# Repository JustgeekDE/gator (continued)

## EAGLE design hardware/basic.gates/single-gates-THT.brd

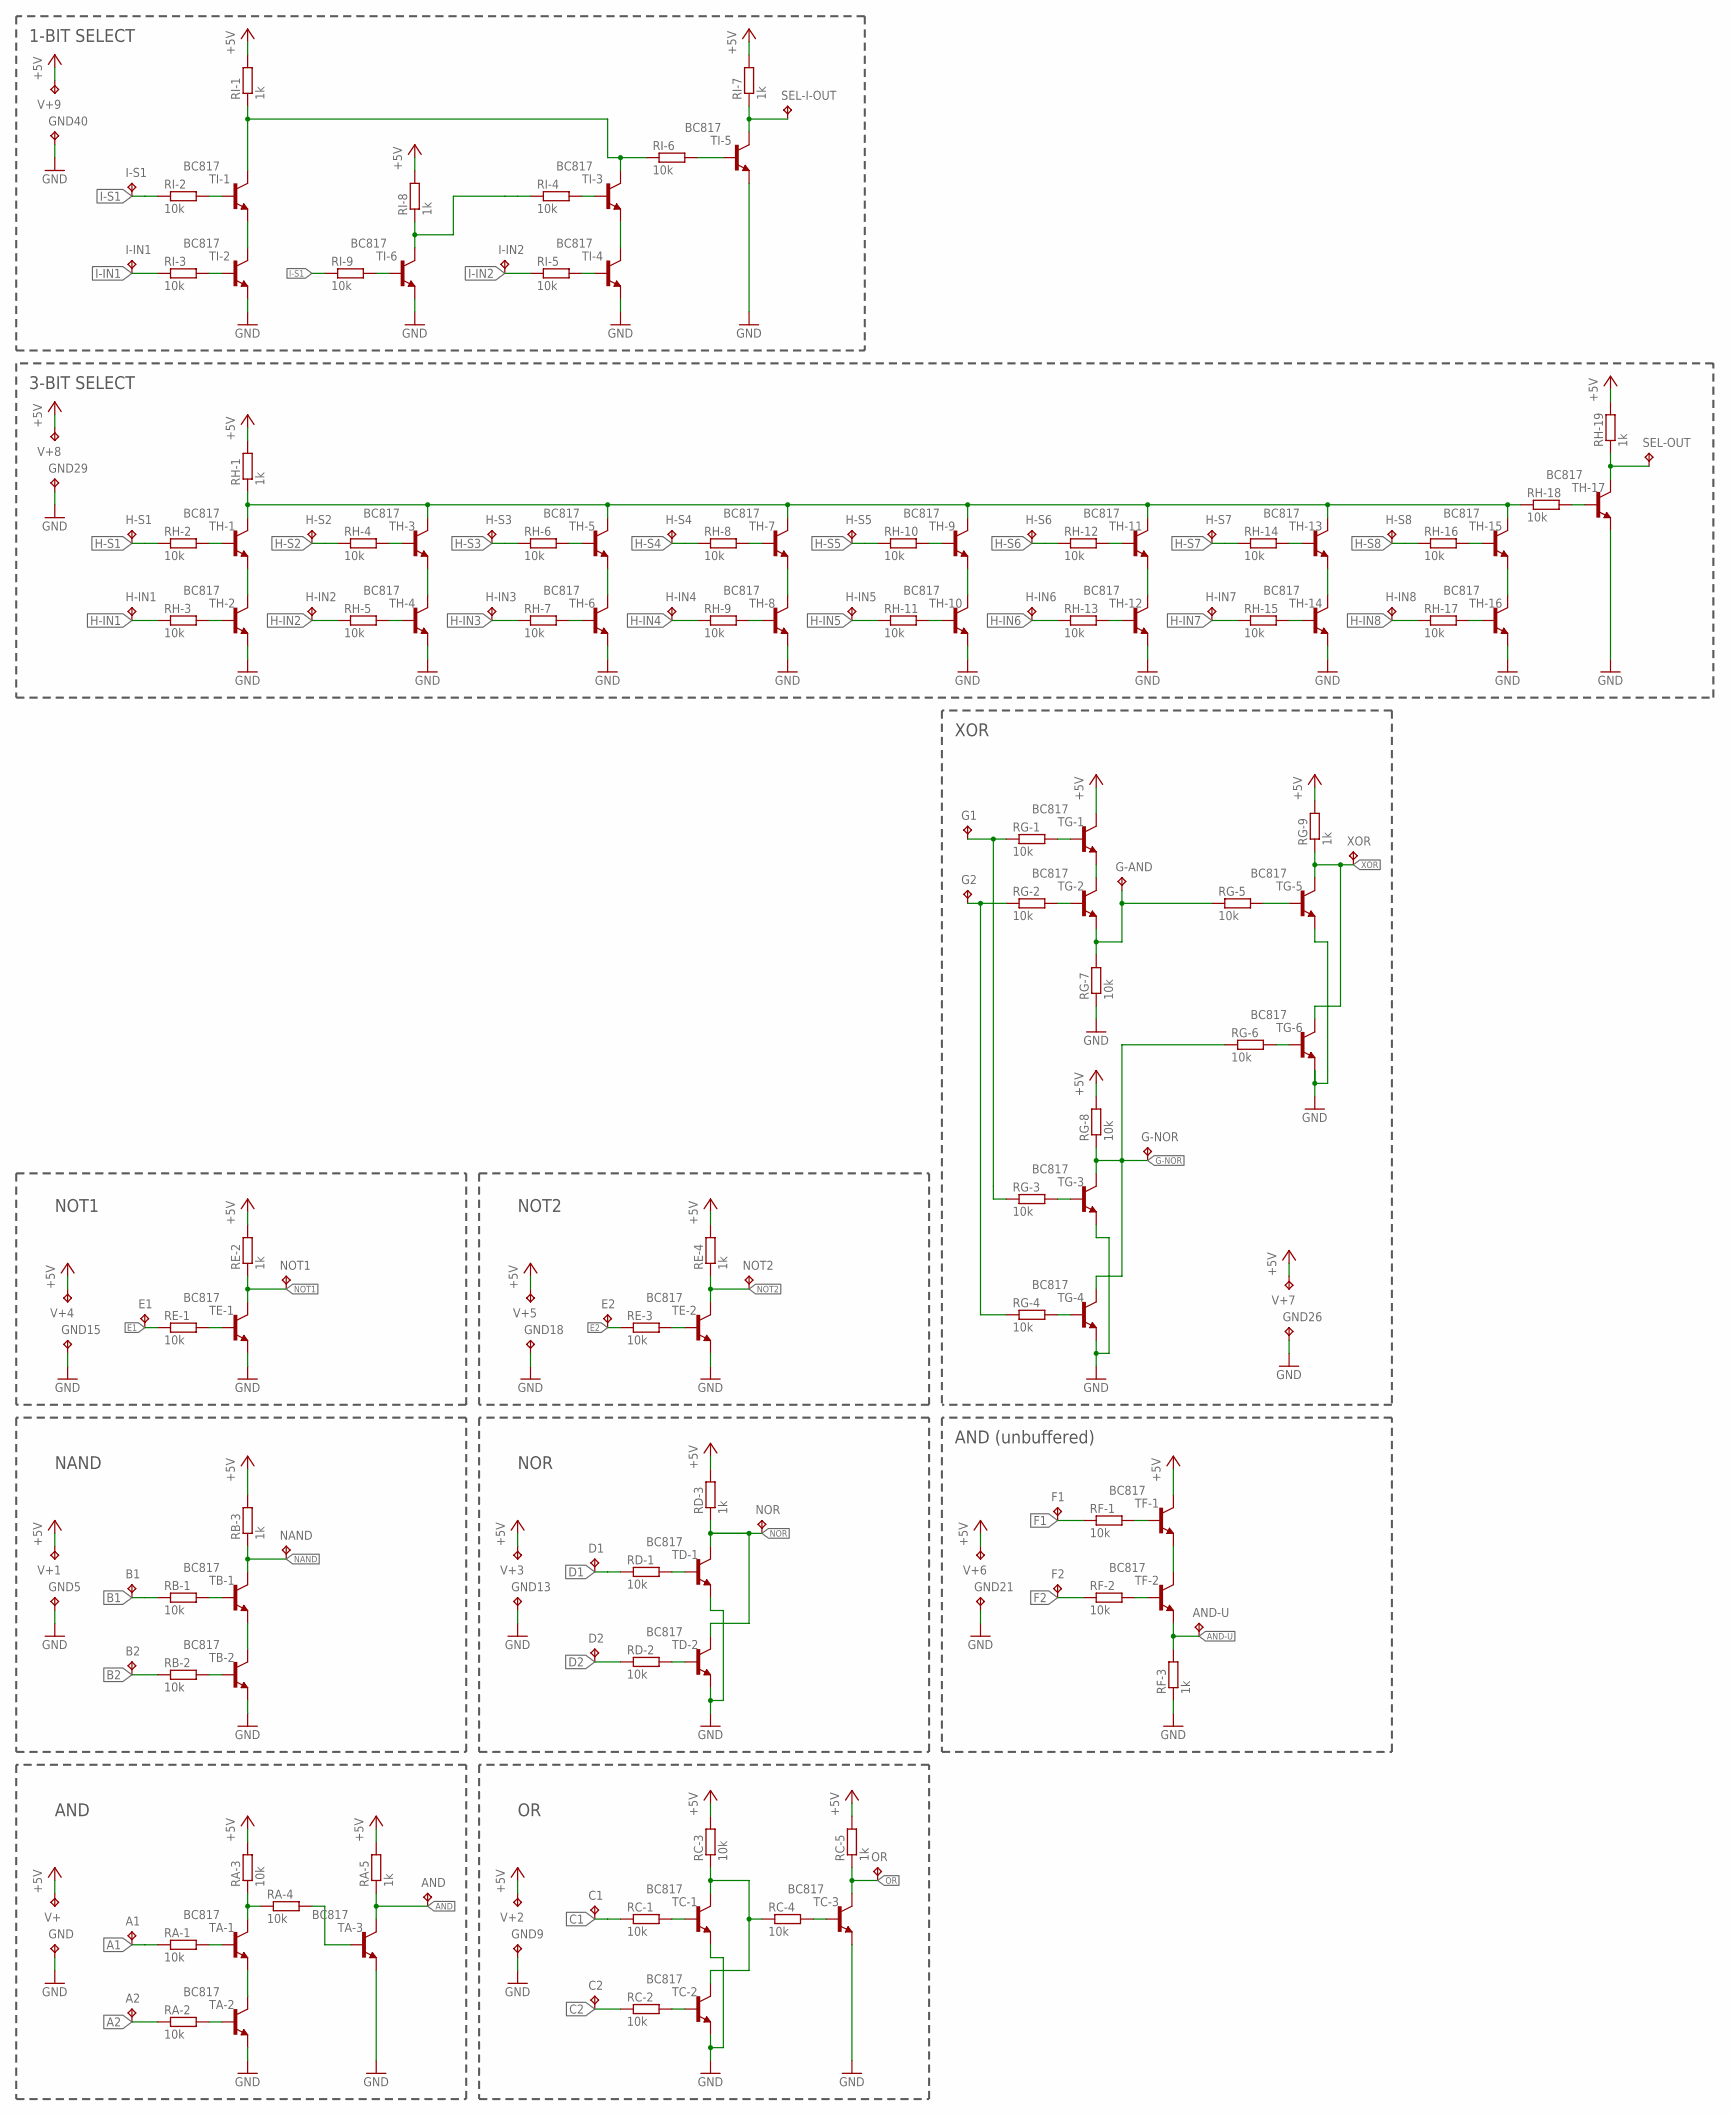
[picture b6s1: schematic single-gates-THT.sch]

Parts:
A1, A2: TPTP07R; TP07R
AND: TPTP07R; TP07R
AND-U: TPTP07R; TP07R
B1, B2: TPTP07R; TP07R
C1, C2: TPTP07R; TP07R
D1, D2: TPTP07R; TP07R
E1, E2: TPTP07R; TP07R
F1, F2: TPTP07R; TP07R
G1, G2: TPTP07R; TP07R
G-AND: TPTP07R; TP07R
G-NOR: TPTP07R; TP07R
GND, GND5, GND9, GND13, GND15, GND18, GND21, GND26, GND29, GND40: TPTP07R; TP07R
H-IN1, H-IN2, H-IN3, H-IN4, H-IN5, H-IN6, H-IN7, H-IN8: TPTP07R; TP07R
H-S1, H-S2, H-S3, H-S4, H-S5, H-S6, H-S7, H-S8: TPTP07R; TP07R
I-IN1, I-IN2: TPTP07R; TP07R
I-S1: TPTP07R; TP07R
NAND: TPTP07R; TP07R
NOR: TPTP07R; TP07R
NOT1, NOT2: TPTP07R; TP07R
OR: TPTP07R; TP07R
RA-1, RA-2, RA-3, RA-4: 10k; 0207/7
RA-5: 1k; 0207/7
RB-1, RB-2: 10k; 0207/7
RB-3: 1k; 0207/7
RC-1, RC-2, RC-3, RC-4: 10k; 0207/7
RC-5: 1k; 0207/7
RD-1, RD-2: 10k; 0207/7
RD-3: 1k; 0207/7
RE-1, RE-3: 10k; 0207/7
RE-2, RE-4: 1k; 0207/7
RF-1, RF-2: 10k; 0207/7
RF-3: 1k; 0207/7
RG-1, RG-2, RG-3, RG-4, RG-5, RG-6, RG-7, RG-8: 10k; 0207/7
RG-9: 1k; 0207/7
RH-1, RH-19: 1k; 0207/7
RH-2, RH-3, RH-4, RH-5, RH-6, RH-7, RH-8, RH-9, RH-10, RH-11, RH-12, RH-13, RH-14, RH-15, RH-16, RH-17, RH-18: 10k; 0207/7
RI-1, RI-7, RI-8: 1k; 0207/7
RI-2, RI-3, RI-4, RI-5, RI-6, RI-9: 10k; 0207/7
SEL-I-OUT: TPTP07R; TP07R
SEL-OUT: TPTP07R; TP07R
TA-1, TA-2, TA-3: BC817; TO92
TB-1, TB-2: BC817; TO92
TC-1, TC-2, TC-3: BC817; TO92
TD-1, TD-2: BC817; TO92
TE-1, TE-2: BC817; TO92
TF-1, TF-2: BC817; TO92
TG-1, TG-2, TG-3, TG-4, TG-5, TG-6: BC817; TO92
TH-1, TH-2, TH-3, TH-4, TH-5, TH-6, TH-7, TH-8, TH-9, TH-10, TH-11, TH-12, TH-13, TH-14, TH-15, TH-16, TH-17: BC817; TO92
TI-1, TI-2, TI-3, TI-4, TI-5, TI-6: BC817; TO92
V+, V+1, V+2, V+3, V+4, V+5, V+6, V+7, V+8, V+9: TPTP07R; TP07R
XOR: TPTP07R; TP07R

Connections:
+5V: RA-3.2, RA-5.2, RB-3.2, RC-3.2, RC-5.2, RD-3.2, RE-2.2, RE-4.2, RG-8.2, RG-9.2, RH-1.2, RH-19.2, RI-1.2, RI-7.2, RI-8.2, TF-1.3 (C), TG-1.3 (C), V+.TP, V+1.TP, V+2.TP, V+3.TP, V+4.TP, V+5.TP, V+6.TP, V+7.TP, V+8.TP, V+9.TP
A1: A1.TP, RA-1.1
A2: A2.TP, RA-2.1
AND: AND.TP, RA-5.1, TA-3.3 (C)
AND-U: AND-U.TP, RF-3.2, TF-2.1 (E)
B1: B1.TP, RB-1.1
B2: B2.TP, RB-2.1
C1: C1.TP, RC-1.1
C2: C2.TP, RC-2.1
D1: D1.TP, RD-1.1
D2: D2.TP, RD-2.1
E1: E1.TP, RE-1.1
E2: E2.TP, RE-3.1
F1: F1.TP, RF-1.1
F2: F2.TP, RF-2.1
G-AND: G-AND.TP, RG-5.1, RG-7.2, TG-2.1 (E)
G-NOR: G-NOR.TP, RG-6.1, RG-8.1, TG-3.3 (C), TG-4.3 (C)
GND: GND.TP, GND5.TP, GND9.TP, GND13.TP, GND15.TP, GND18.TP, GND21.TP, GND26.TP, GND29.TP, GND40.TP, RF-3.1, RG-7.1, TA-2.1 (E), TA-3.1 (E), TB-2.1 (E), TC-1.1 (E), TC-2.1 (E), TC-3.1 (E), TD-1.1 (E), TD-2.1 (E), TE-1.1 (E), TE-2.1 (E), TG-3.1 (E), TG-4.1 (E), TG-5.1 (E), TG-6.1 (E), TH-2.1 (E), TH-4.1 (E), TH-6.1 (E), TH-8.1 (E), TH-10.1 (E), TH-12.1 (E), TH-14.1 (E), TH-16.1 (E), TH-17.1 (E), TI-2.1 (E), TI-4.1 (E), TI-5.1 (E), TI-6.1 (E)
H-IN1: H-IN1.TP, RH-3.1
H-IN2: H-IN2.TP, RH-5.1
H-IN3: H-IN3.TP, RH-7.1
H-IN4: H-IN4.TP, RH-9.1
H-IN5: H-IN5.TP, RH-11.1
H-IN6: H-IN6.TP, RH-13.1
H-IN7: H-IN7.TP, RH-15.1
H-IN8: H-IN8.TP, RH-17.1
H-S1: H-S1.TP, RH-2.1
H-S2: H-S2.TP, RH-4.1
H-S3: H-S3.TP, RH-6.1
H-S4: H-S4.TP, RH-8.1
H-S5: H-S5.TP, RH-10.1
H-S6: H-S6.TP, RH-12.1
H-S7: H-S7.TP, RH-14.1
H-S8: H-S8.TP, RH-16.1
I-IN1: I-IN1.TP, RI-3.1
I-IN2: I-IN2.TP, RI-5.1
I-S1: I-S1.TP, RI-2.1, RI-9.1
I-S2: RI-4.1, RI-8.1, TI-6.3 (C)
unnamed: RA-1.2, TA-1.2 (B)
unnamed: RA-3.1, RA-4.1, TA-1.3 (C)
unnamed: RA-2.2, TA-2.2 (B)
unnamed: TA-1.1 (E), TA-2.3 (C)
unnamed: RB-1.2, TB-1.2 (B)
unnamed: RB-2.2, TB-2.2 (B)
unnamed: RC-1.2, TC-1.2 (B)
unnamed: TB-1.1 (E), TB-2.3 (C)
unnamed: RC-2.2, TC-2.2 (B)
unnamed: RC-4.2, TC-3.2 (B)
unnamed: RC-3.1, RC-4.1, TC-1.3 (C), TC-2.3 (C)
unnamed: RD-1.2, TD-1.2 (B)
unnamed: RD-2.2, TD-2.2 (B)
unnamed: RE-1.2, TE-1.2 (B)
unnamed: RA-4.2, TA-3.2 (B)
unnamed: RE-3.2, TE-2.2 (B)
unnamed: RF-1.2, TF-1.2 (B)
unnamed: RF-2.2, TF-2.2 (B)
unnamed: TG-1.1 (E), TG-2.3 (C)
unnamed: TF-1.1 (E), TF-2.3 (C)
unnamed: RG-1.2, TG-1.2 (B)
unnamed: RG-2.2, TG-2.2 (B)
unnamed: RG-4.2, TG-4.2 (B)
unnamed: RG-3.2, TG-3.2 (B)
unnamed: RG-6.2, TG-6.2 (B)
unnamed: RG-5.2, TG-5.2 (B)
unnamed: RH-2.2, TH-1.2 (B)
unnamed: RH-3.2, TH-2.2 (B)
unnamed: TH-1.1 (E), TH-2.3 (C)
unnamed: G1.TP, RG-1.1, RG-3.1
unnamed: G2.TP, RG-2.1, RG-4.1
unnamed: RH-4.2, TH-3.2 (B)
unnamed: RH-5.2, TH-4.2 (B)
unnamed: TH-3.1 (E), TH-4.3 (C)
unnamed: RH-6.2, TH-5.2 (B)
unnamed: RH-7.2, TH-6.2 (B)
unnamed: TH-5.1 (E), TH-6.3 (C)
unnamed: RH-8.2, TH-7.2 (B)
unnamed: RH-9.2, TH-8.2 (B)
unnamed: TH-7.1 (E), TH-8.3 (C)
unnamed: RH-10.2, TH-9.2 (B)
unnamed: RH-11.2, TH-10.2 (B)
unnamed: TH-9.1 (E), TH-10.3 (C)
unnamed: RH-12.2, TH-11.2 (B)
unnamed: RH-13.2, TH-12.2 (B)
unnamed: TH-11.1 (E), TH-12.3 (C)
unnamed: RH-14.2, TH-13.2 (B)
unnamed: RH-15.2, TH-14.2 (B)
unnamed: TH-13.1 (E), TH-14.3 (C)
unnamed: RH-16.2, TH-15.2 (B)
unnamed: RH-17.2, TH-16.2 (B)
unnamed: TH-15.1 (E), TH-16.3 (C)
unnamed: RI-2.2, TI-1.2 (B)
unnamed: RH-18.2, TH-17.2 (B)
unnamed: RI-3.2, TI-2.2 (B)
unnamed: TI-1.1 (E), TI-2.3 (C)
unnamed: RI-4.2, TI-3.2 (B)
unnamed: RI-5.2, TI-4.2 (B)
unnamed: TI-3.1 (E), TI-4.3 (C)
unnamed: RI-6.2, TI-5.2 (B)
unnamed: RI-9.2, TI-6.2 (B)
NAND: NAND.TP, RB-3.1, TB-1.3 (C)
NOR: NOR.TP, RD-3.1, TD-1.3 (C), TD-2.3 (C)
NOT1: NOT1.TP, RE-2.1, TE-1.3 (C)
NOT2: NOT2.TP, RE-4.1, TE-2.3 (C)
OR: OR.TP, RC-5.1, TC-3.3 (C)
SEL_INT: RH-1.1, RH-18.1, TH-1.3 (C), TH-3.3 (C), TH-5.3 (C), TH-7.3 (C), TH-9.3 (C), TH-11.3 (C), TH-13.3 (C), TH-15.3 (C)
SEL_INT1: RI-1.1, RI-6.1, TI-1.3 (C), TI-3.3 (C)
SEL_OUT: RH-19.1, SEL-OUT.TP, TH-17.3 (C)
SEL_OUT1: RI-7.1, SEL-I-OUT.TP, TI-5.3 (C)
XOR: RG-9.1, TG-5.3 (C), TG-6.3 (C), XOR.TP

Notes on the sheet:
AND
NAND
NOR
NOT1
NOT2
AND (unbuffered)
XOR
3-BIT SELECT
1-BIT SELECT

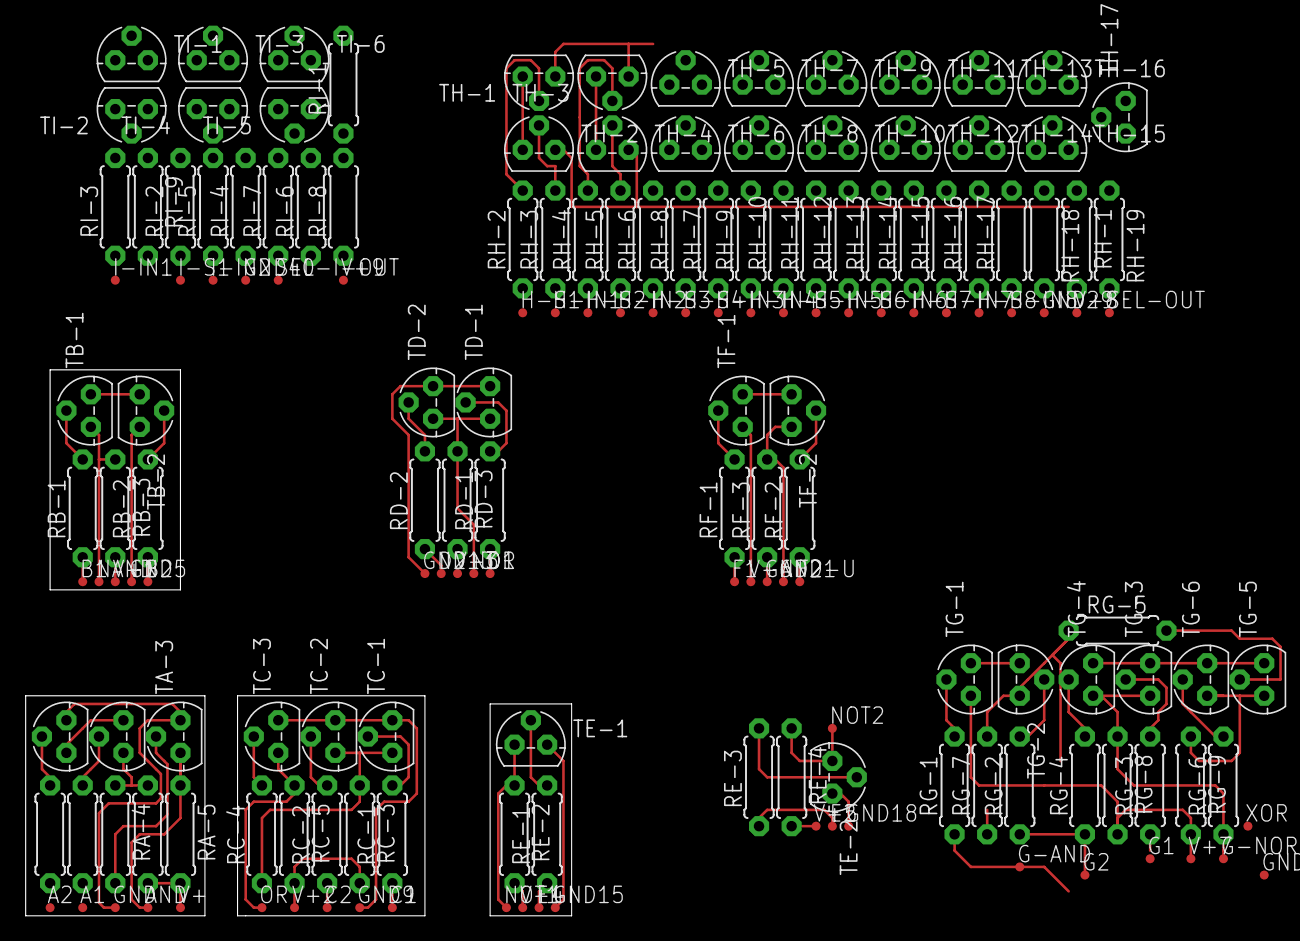
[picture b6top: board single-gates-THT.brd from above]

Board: 2 copper layers, 42.5 x 42.5 mm, 168 parts (0 on the bottom side), 109 nets.

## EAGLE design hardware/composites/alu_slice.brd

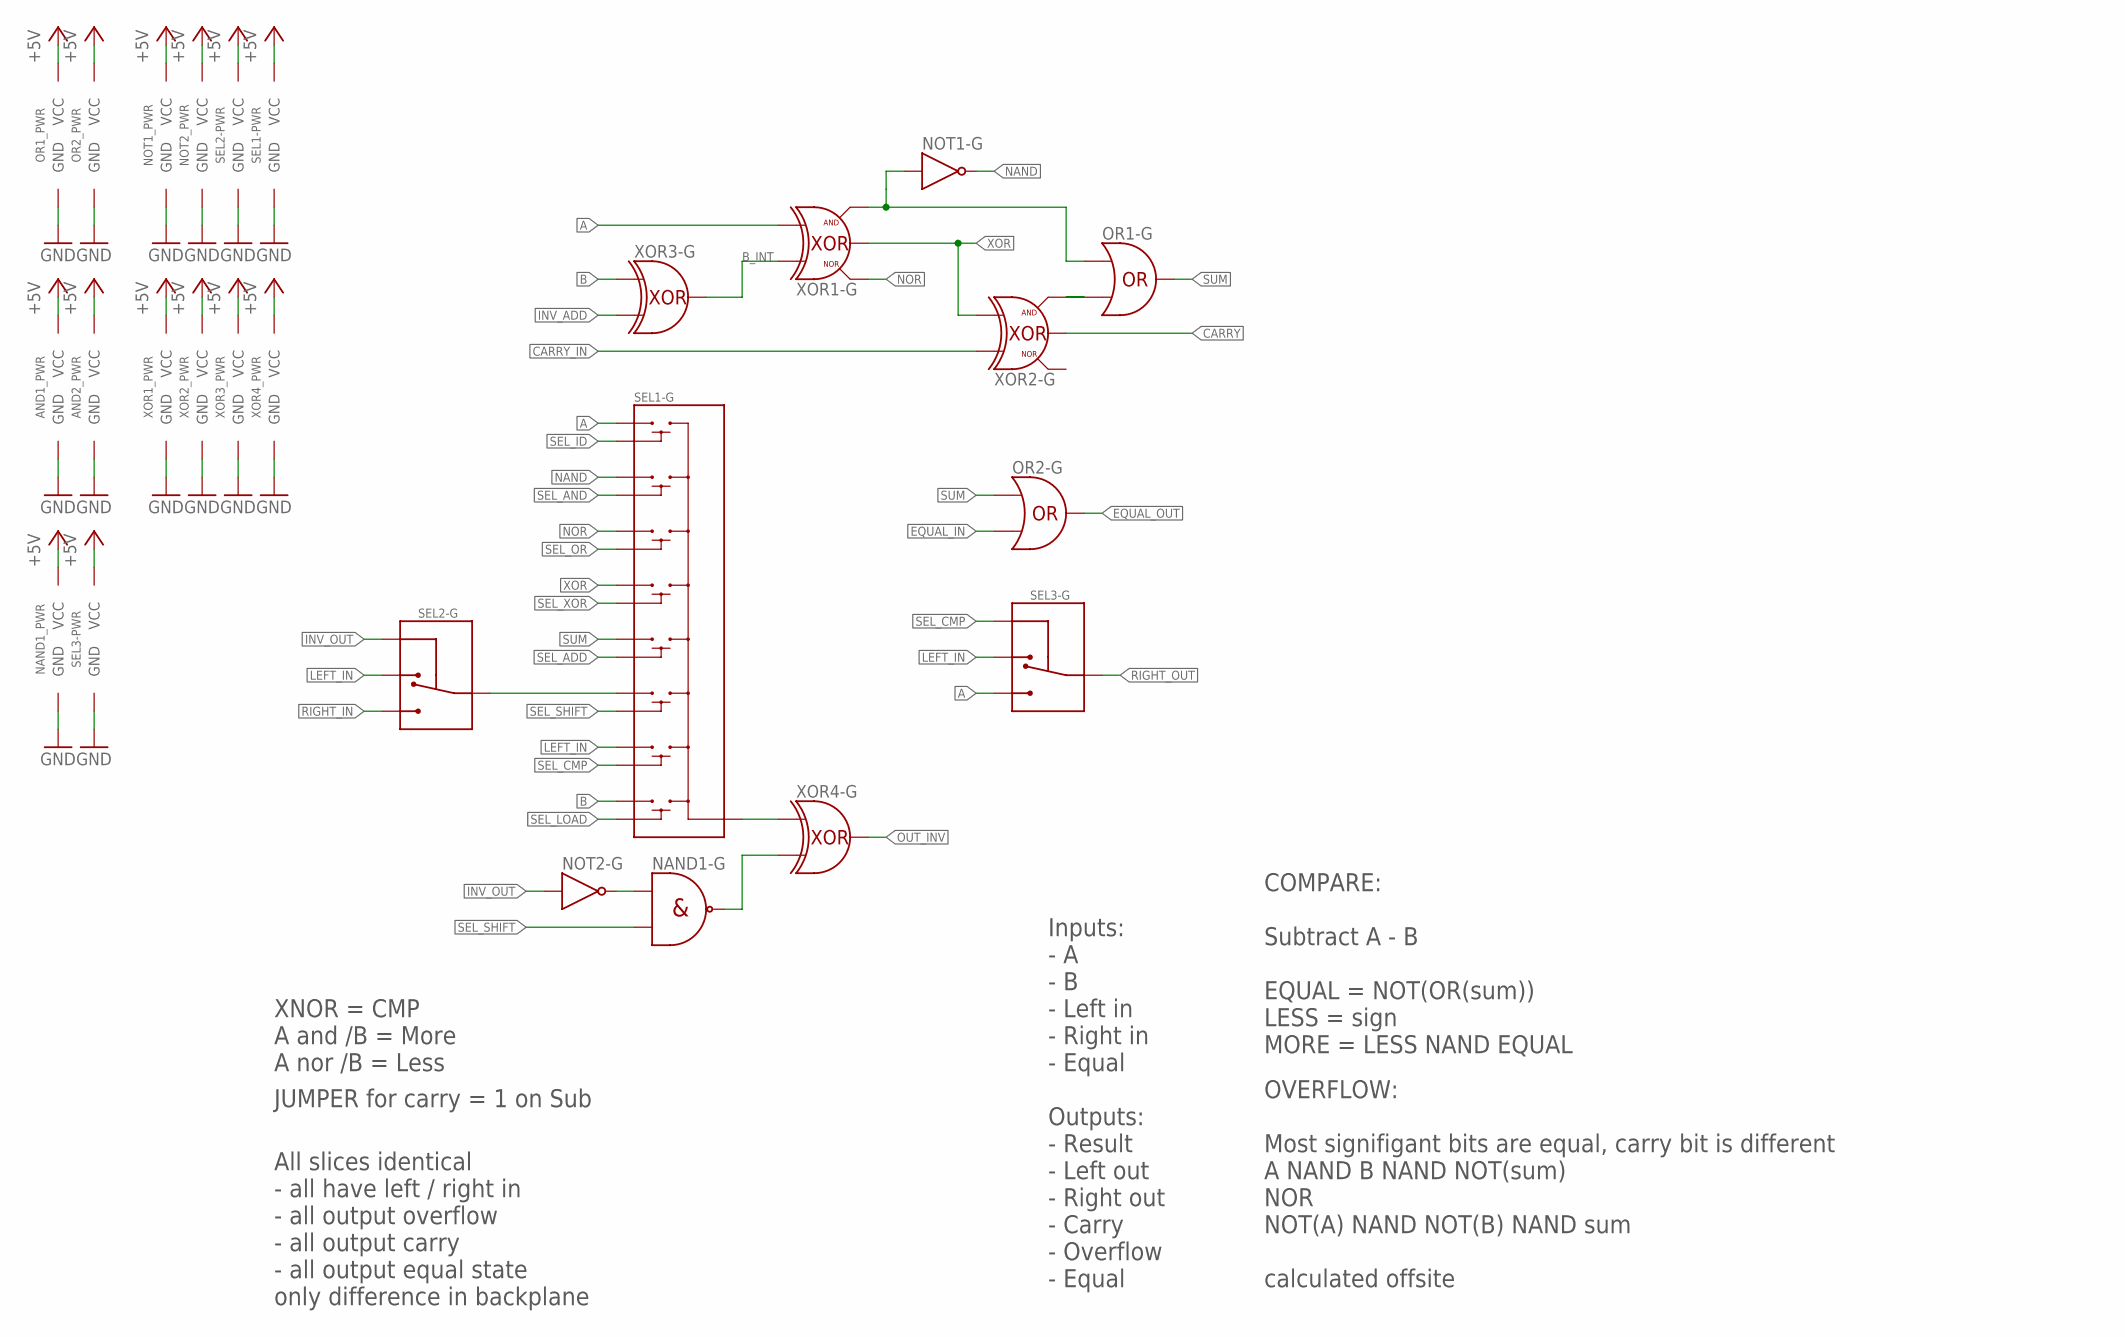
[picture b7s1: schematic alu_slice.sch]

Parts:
AND1, AND2: AND-UNBUF; AND-2-UNBUF
NAND1: NAND; NAND-2
NOT1, NOT2: NOT-VERTICAL
OR1, OR2: OR; OR-2
SEL1: SELECTOR; SELECTOR-8_BIT-NOMUX
SEL2, SEL3: SELECTOR-2_LANES; SELECTOR-2-LANE-NOMUX
XOR1, XOR2: EX-XOR; XOR-2-EX2
XOR3, XOR4: XOR; XOR-2-EX2

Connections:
+5V: AND1.OUT3 (VCC), AND2.OUT3 (VCC), NAND1.OUT1 (VCC), NOT1.OUT3 (VCC), NOT2.OUT3 (VCC), OR1.OUT3 (VCC), OR2.OUT3 (VCC), SEL1.V+ (VCC), SEL2.V+ (VCC), SEL3.V+ (VCC), XOR1.OUT1 (VCC), XOR2.OUT1 (VCC), XOR3.OUT1 (VCC), XOR4.OUT1 (VCC)
A: SEL1.IN1, SEL3.IN2, XOR1.B
B: SEL1.IN8, XOR3.A
B_INT: XOR1.A, XOR3.OUT4 (OUT)
CARRY: XOR2.OUT4 (OUT)
CARRY_IN: XOR2.A
EQUAL_IN: OR2.B
EQUAL_OUT: OR2.OUT1 (OUT)
GND: AND1.OUT1 (GND), AND2.OUT1 (GND), NAND1.OUT3 (GND), NOT1.OUT2 (GND), NOT2.OUT2 (GND), OR1.OUT2 (GND), OR2.OUT2 (GND), SEL1.GND, SEL2.GND, SEL3.GND, XOR1.OUT5 (GND), XOR2.OUT5 (GND), XOR3.OUT5 (GND), XOR4.OUT5 (GND)
INV_ADD: XOR3.B
INV_OUT: NOT2.IN, SEL2.SEL
LEFT_IN: SEL1.IN7, SEL2.IN1, SEL3.IN1
unnamed: NOT1.IN, OR1.A, XOR1.OUT2 (AND)
unnamed: OR1.B, XOR2.OUT2 (AND)
unnamed: SEL1.IN6, SEL2.OUT
unnamed: NAND1.OUT2 (OUT), XOR4.B
unnamed: NAND1.B (A), NOT2.OUT1 (OUT)
NAND: NOT1.OUT1 (OUT), SEL1.IN2
NOR: SEL1.IN3, XOR1.OUT3 (NOR)
OUT: SEL1.OUT, XOR4.A
OUT_INV: XOR4.OUT4 (OUT)
RIGHT_IN: SEL2.IN2
RIGHT_OUT: SEL3.OUT
SEL_ADD: SEL1.SEL5
SEL_AND: SEL1.SEL2
SEL_CMP: SEL1.SEL7, SEL3.SEL
SEL_ID: SEL1.SEL1
SEL_LOAD: SEL1.SEL8
SEL_OR: SEL1.SEL3
SEL_SHIFT: NAND1.A (B), SEL1.SEL6
SEL_XOR: SEL1.SEL4
SUM: OR1.OUT1 (OUT), OR2.A, SEL1.IN5
XOR: SEL1.IN4, XOR1.OUT4 (OUT), XOR2.B

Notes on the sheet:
XNOR = CMP
A and /B = More A nor /B = Less
JUMPER for carry = 1 on Sub
All slices identical - all have left / right in - all output overflow - all output carry - all output equal state only difference in backplane
Inputs: - A - B - Left in - Right in - Equal Outputs: - Result - Left out - Right out - Carry - Overflow - Equal
COMPARE: Subtract A - B EQUAL = NOT(OR(sum)) LESS = sign MORE = LESS NAND EQUAL
OVERFLOW: Most signifigant bits are equal, carry bit is different A NAND B NAND NOT(sum) NOR NOT(A) NAND NOT(B) NAND sum calculated offsite

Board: 2 copper layers, 14 parts (0 on the bottom side), 19 nets, no tracks yet.

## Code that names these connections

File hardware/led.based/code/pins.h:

#ifndef __PINS_H
#define __PINS_H


#define SET_BIT(port,bit)   (port |=  (1 << bit))
#define CLEAR_BIT(port,bit) (port &= ~(1 << bit))
#define READ_BIT(port,bit)  ((port & (1 << bit)) ? 1 : 0)



/* User interface Buttons */
#define BUTTON_PORT PORTB
#define BUTTON_DDR  DDRB
#define BUTTON_PIN  PINB
#define BUTTON_BIT  PB2

/* User Interface LEDs */
#define LED_PORT PORTA
#define LED_DDR  DDRA
#define LED_PIN  PINA

#define LED_0   0
#define LED_0_A PA0
#define LED_0_C PA1
#define LED_0_ADC 0

#define LED_1   2
#define LED_1_A PA2
#define LED_1_C PA3
#define LED_1_ADC 2

#define LED_2   4
#define LED_2_A PA4
#define LED_2_C PA5
#define LED_2_ADC 4

#define LED_3   6
#define LED_3_A PA6
#define LED_3_C PA7
#define LED_3_ADC 6

#define LED_AN(led) (led << 1) 
#define LED_CAT(led) ((led << 1)+1) 

#define LED_Z 0
#define LED_IN 8
#define LED_ON 14
#define LED_OFF 10
#define LED_READ 8
#define LED_CHARGE 11
#define LED_REVERSE 11

#define LED_PHOTODIODE 3
#define LED_SOLAR 2

/* LED states *
 * 0  = Z Z = 00 00
 * 1  = Z P = 00 01
 * 2  = Z L = 00 10
 * 3  = Z H = 00 11
 * 4  = P Z = 01 00
 * 5  = P P = 01 01
 * 6  = P L = 01 10
 * 7  = P H = 01 11
 * 8  = L Z = 10 00
 * 9  = L P = 10 01
 * 10 = L L = 10 10
 * 11 = L H = 10 11 
 * 12 = H Z = 11 00
 * 13 = H P = 11 01
 * 14 = H L = 11 10
 * 15 = H H = 11 11
 */

#endif

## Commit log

2015-07-08 Basic eagle ignores
2015-07-08 initial checkin
2015-07-08 added old individual components
2015-07-08 added old led based gates
